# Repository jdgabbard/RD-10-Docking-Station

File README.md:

# RD-10-Docking-Station
A DIY Docking Station for the Casio MX-10 / MX-15 MSX computers

***REV 2 Board Added to Repository***

***See Build Notes file for special instructions!***

Designed to replace or substitute the KB-10 or KB-15 docking station. Future releases may expand this design. For now, consider it a way to have more than one catridge in your MX-10 or MX-15 at a time.  ***For details, see below.***

Features include:<br><br>
-The ability to directly power the Mx-10 / MX-15 / MX-101 computer from the RD-10 Docking Station.<br>
-Integrated Power Switch for turning on the MX-10.<br>
-Experimental Audio Input Jack (2.5mm) for injecting music into the MSX audio amplifier.<br>
-External Power Connector, allowing powering of Floppy Drives directly from the Docking Station.<br>
-Two Primary Slots<br>
-Construction consisting of off the shelf TTL logic, and current production PLD (ATF22V10).<br>
-Implements +12v/-12v rails, so Audio Cartridges work correctly (MX-10 did not do this on it's one cartridge slot).<br><br>

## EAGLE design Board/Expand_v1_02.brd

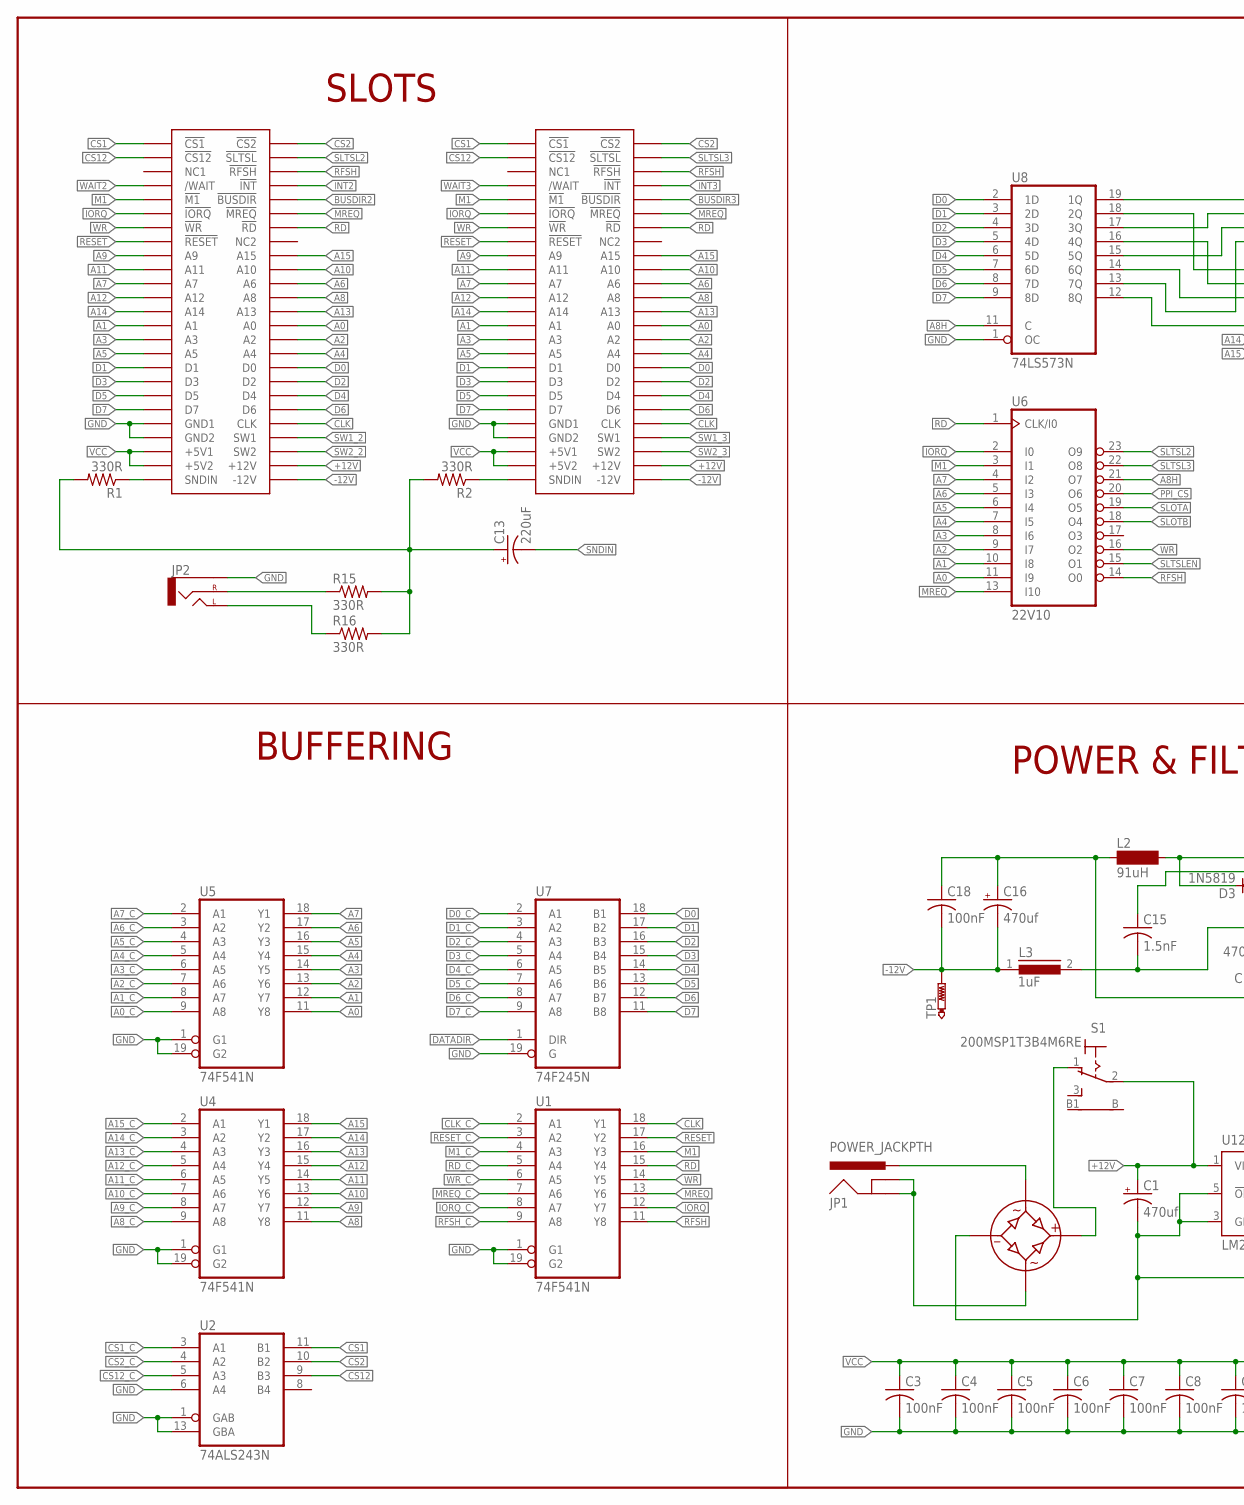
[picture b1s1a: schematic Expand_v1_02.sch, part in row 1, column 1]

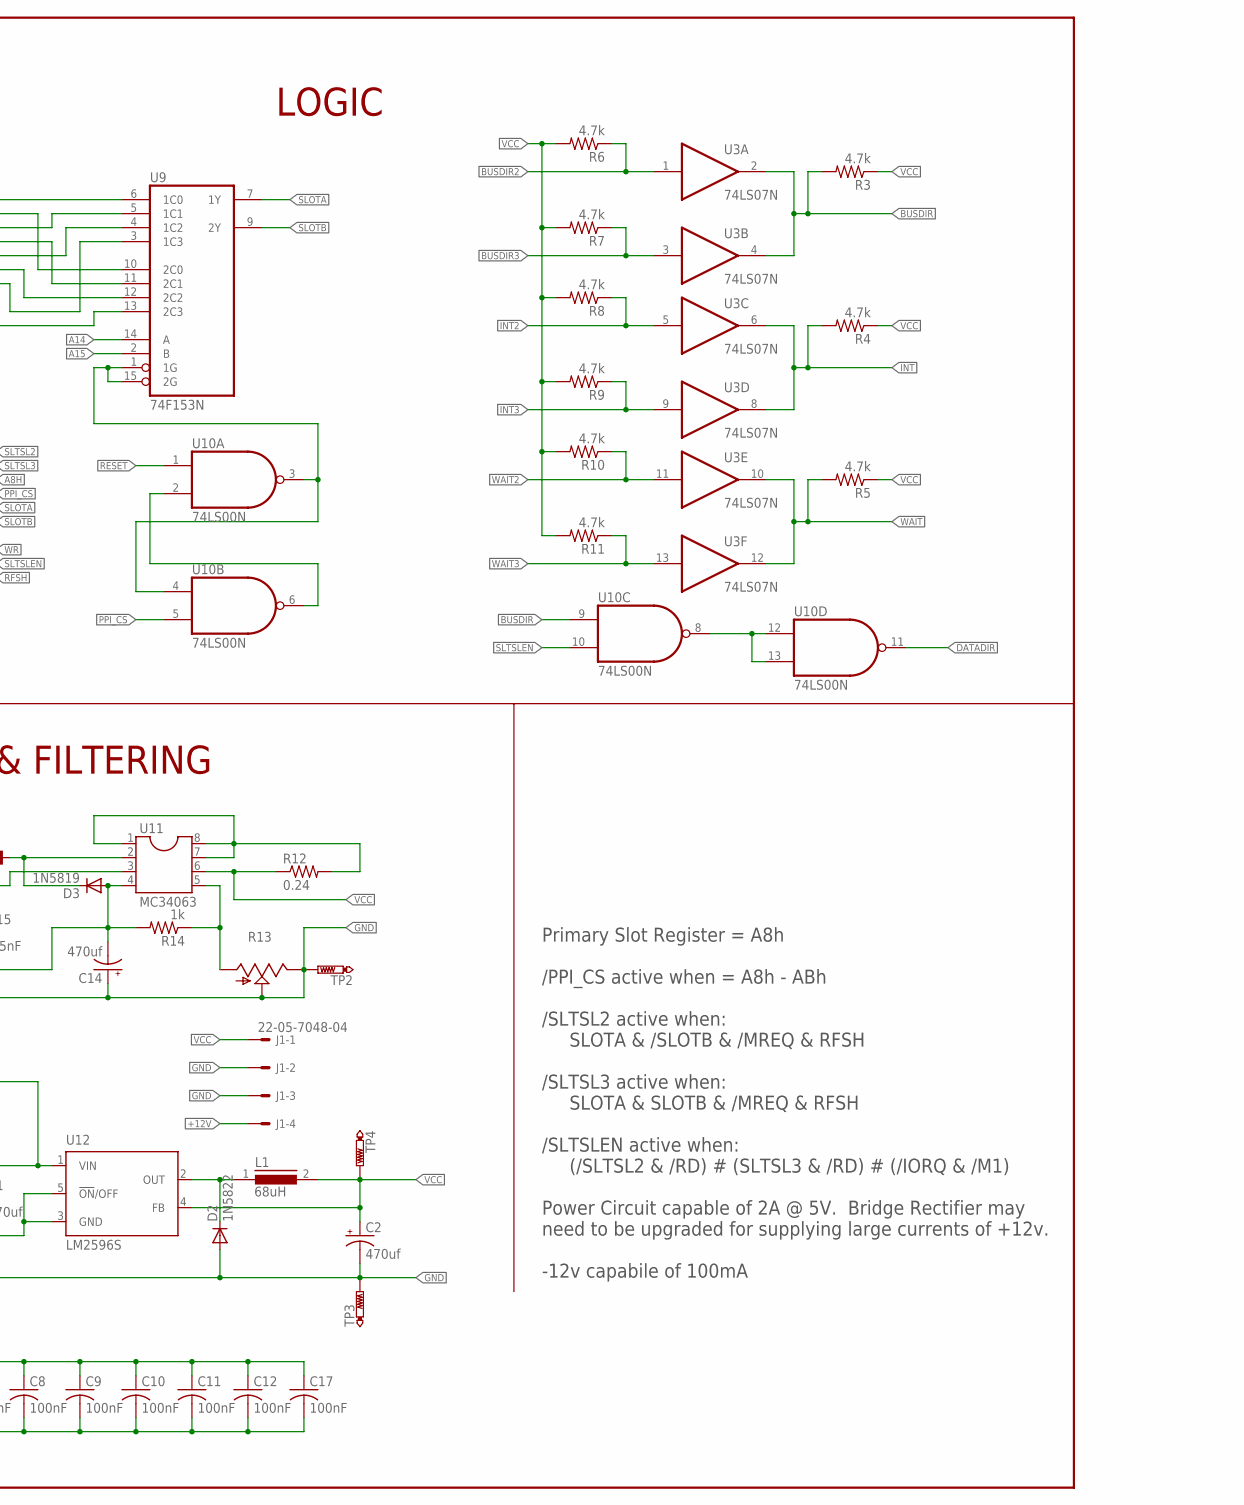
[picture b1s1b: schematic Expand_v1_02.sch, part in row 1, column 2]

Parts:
C1, C2, C14, C16: 470uf; E5-10,5
C3, C4, C5, C6, C7, C8, C9, C10, C11, C12, C17, C18: 100nF; C050-030X075
C13: 220uF; E2-4
C15: 1.5nF; C050-030X075
CONN2, CONN3: MSX_CART_SLOT; CART_SLOT
D1: 2W10
D2: 1N5822; DO201-15
D3: 1N5819; DO15-12
J1: 22-05-7048-04; 7395-04
JP1: POWER_JACKPTH; POWER_JACK_PTH
JP2: AUDIO-JACK1:1; STEREOJACK2.5MM
L1: 68uH; A26GFC
L2: 91uH; BS11
L3: 1uF; MCC10
R1, R2, R15, R16: 330R; 0207/7
R3, R4, R5, R6, R7, R8, R9, R10, R11: 4.7k; 0207/7
R12: 0.24; 0207/10
R13: TRIM_US-RJ9W; RJ9W
R14: 1k; 0207/7
S1: 200MSP1T3B4M6RE; 9070-1W
TP1, TP2, TP3, TP4: PTR1B2,54; B2,54
U1, U4, U5: 74F541N; DIL20
U2: 74ALS243N; DIL14
U3: 74LS07N; DIL14
U6: 22V10; DIL24-3
U7: 74F245N; DIL20
U8: 74LS573N; DIL20
U9: 74F153N; DIL16
U10: 74LS00N; DIL14
U11: MC34063; DIL08
U12: LM2596S; TO263-5

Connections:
!A8H: U6.21 (O7), U8.11 (C)
!BUSDIR: R3.2, U3.2 (O), U3.4 (O), U10.9 (I0)
!BUSDIR2: CONN2.P$10 (!BUSDIR), R6.1, U3.1 (I)
!BUSDIR3: CONN3.P$10 (!BUSDIR), R7.1, U3.3 (I)
!CS1: CONN2.P$1 (!CS1), CONN3.P$1 (!CS1), U2.11 (B1)
!CS1_C: U2.3 (A1)
!CS2: CONN2.P$2 (!CS2), CONN3.P$2 (!CS2), U2.10 (B2)
!CS2_C: U2.4 (A2)
!CS12: CONN2.P$3 (!CS12), CONN3.P$3 (!CS12), U2.9 (B3)
!CS12_C: U2.5 (A3)
!DATADIR: U7.1 (DIR), U10.11 (O)
!INT: R4.2, U3.6 (O), U3.8 (O)
!INT2: CONN2.P$8 (!INT), R8.1, U3.5 (I)
!INT3: CONN3.P$8 (!INT), R9.1, U3.9 (I)
!IORQ: CONN2.P$11 (!IORQ), CONN3.P$11 (!IORQ), U1.12 (Y7), U6.2 (I0)
!IORQ_C: U1.8 (A7)
!M1: CONN2.P$9 (!M1), CONN3.P$9 (!M1), U1.16 (Y3), U6.3 (I1)
!M1_C: U1.4 (A3)
!MREQ: CONN2.P$12 (!MREQ), CONN3.P$12 (!MREQ), U1.13 (Y6), U6.13 (I10)
!MREQ_C: U1.7 (A6)
!PPI_CS: U6.20 (O6), U10.5 (I1)
!RD: CONN2.P$14 (!RD), CONN3.P$14 (!RD), U1.15 (Y4), U6.1 (CLK/I0)
!RD_C: U1.5 (A4)
!RESET: CONN2.P$15 (!RESET), CONN3.P$15 (!RESET), U1.17 (Y2), U10.1 (I0)
!RESET_C: U1.3 (A2)
!RFSH: CONN2.P$6 (!RFSH), CONN3.P$6 (!RFSH), U1.11 (Y8), U6.14 (O0)
!RFSH_C: U1.9 (A8)
!SLTSL2: CONN2.P$4 (!SLTSL), U6.23 (O9)
!SLTSL3: CONN3.P$4 (!SLTSL), U6.22 (O8)
!SLTSLEN: U6.15 (O1), U10.10 (I1)
!WAIT: R5.2, U3.10 (O), U3.12 (O)
!WAIT2: CONN2.P$7 (/WAIT), R10.1, U3.11 (I)
!WAIT3: CONN3.P$7 (/WAIT), R11.1, U3.13 (I)
!WR: CONN2.P$13 (!WR), CONN3.P$13 (!WR), U1.14 (Y5), U6.16 (O2)
!WR_C: U1.6 (A5)
+12V: C1.+, CONN2.P$48 (+12V), CONN3.P$48 (+12V), J1.4, S1.2, U12.1 (VIN)
-12V: C16.-, C18.2, CONN2.P$50 (-12V), CONN3.P$50 (-12V), L3.1, TP1.TP
A0: CONN2.P$28 (A0), CONN3.P$28 (A0), U5.11 (Y8), U6.11 (I9)
A0_C: U5.9 (A8)
A1: CONN2.P$27 (A1), CONN3.P$27 (A1), U5.12 (Y7), U6.10 (I8)
A1_C: U5.8 (A7)
A2: CONN2.P$30 (A2), CONN3.P$30 (A2), U5.13 (Y6), U6.9 (I7)
A2_C: U5.7 (A6)
A3: CONN2.P$29 (A3), CONN3.P$29 (A3), U5.14 (Y5), U6.8 (I6)
A3_C: U5.6 (A5)
A4: CONN2.P$32 (A4), CONN3.P$32 (A4), U5.15 (Y4), U6.7 (I5)
A4_C: U5.5 (A4)
A5: CONN2.P$31 (A5), CONN3.P$31 (A5), U5.16 (Y3), U6.6 (I4)
A5_C: U5.4 (A3)
A6: CONN2.P$22 (A6), CONN3.P$22 (A6), U5.17 (Y2), U6.5 (I3)
A6_C: U5.3 (A2)
A7: CONN2.P$21 (A7), CONN3.P$21 (A7), U5.18 (Y1), U6.4 (I2)
A7_C: U5.2 (A1)
A8: CONN2.P$24 (A8), CONN3.P$24 (A8), U4.11 (Y8)
A8_C: U4.9 (A8)
A9: CONN2.P$17 (A9), CONN3.P$17 (A9), U4.12 (Y7)
A9_C: U4.8 (A7)
A10: CONN2.P$20 (A10), CONN3.P$20 (A10), U4.13 (Y6)
A10_C: U4.7 (A6)
A11: CONN2.P$19 (A11), CONN3.P$19 (A11), U4.14 (Y5)
A11_C: U4.6 (A5)
A12: CONN2.P$23 (A12), CONN3.P$23 (A12), U4.15 (Y4)
A12_C: U4.5 (A4)
A13: CONN2.P$26 (A13), CONN3.P$26 (A13), U4.16 (Y3)
A13_C: U4.4 (A3)
A14: CONN2.P$25 (A14), CONN3.P$25 (A14), U4.17 (Y2), U9.14 (A)
A14_C: U4.3 (A2)
A15: CONN2.P$18 (A15), CONN3.P$18 (A15), U4.18 (Y1), U9.2 (B)
A15_C: U4.2 (A1)
CLK: CONN2.P$42 (CLK), CONN3.P$42 (CLK), U1.18 (Y1)
CLK_C: U1.2 (A1)
D0: CONN2.P$34 (D0), CONN3.P$34 (D0), U7.18 (B1), U8.2 (1D)
D0_C: U7.2 (A1)
D1: CONN2.P$33 (D1), CONN3.P$33 (D1), U7.17 (B2), U8.3 (2D)
D1_C: U7.3 (A2)
D2: CONN2.P$36 (D2), CONN3.P$36 (D2), U7.16 (B3), U8.4 (3D)
D2_C: U7.4 (A3)
D3: CONN2.P$35 (D3), CONN3.P$35 (D3), U7.15 (B4), U8.5 (4D)
D3_C: U7.5 (A4)
D4: CONN2.P$38 (D4), CONN3.P$38 (D4), U7.14 (B5), U8.6 (5D)
D4_C: U7.6 (A5)
D5: CONN2.P$37 (D5), CONN3.P$37 (D5), U7.13 (B6), U8.7 (6D)
D5_C: U7.7 (A6)
D6: CONN2.P$40 (D6), CONN3.P$40 (D6), U7.12 (B7), U8.8 (7D)
D6_C: U7.8 (A7)
D7: CONN2.P$39 (D7), CONN3.P$39 (D7), U7.11 (B8), U8.9 (8D)
D7_C: U7.9 (A8)
GND: C1.-, C2.-, C3.2, C4.2, C5.2, C6.2, C7.2, C8.2, C9.2, C10.2, C11.2, C12.2, C14.+, C16.+, C17.2, C18.1, CONN2.P$41 (GND1), CONN2.P$43 (GND2), CONN3.P$41 (GND1), CONN3.P$43 (GND2), D1.P$4, D2.A, J1.2, J1.3, JP2.5 (SLEEVE), L2.1, R13.E, R13.S, TP2.TP, TP3.TP, U1.1 (G1), U1.10 (GND), U1.19 (G2), U2.1 (GAB), U2.6 (A4), U2.7 (GND), U2.13 (GBA), U3.7 (GND), U4.1 (G1), U4.10 (GND), U4.19 (G2), U5.1 (G1), U5.10 (GND), U5.19 (G2), U6.12 (GND), U7.10 (GND), U7.19 (G), U8.1 (OC), U8.10 (GND), U9.8 (GND), U10.7 (GND), U12.3 (GND), U12.5 (!ON!/OFF)
unnamed: CONN3.P$49 (SNDIN), R2.1
unnamed: CONN2.P$49 (SNDIN), R1.1
unnamed: U8.19 (1Q), U9.6 (1C0)
unnamed: C13.+, R1.2, R2.2, R15.2, R16.2
unnamed: U8.18 (2Q), U9.10 (2C0)
unnamed: U8.17 (3Q), U9.5 (1C1)
unnamed: U8.16 (4Q), U9.11 (2C1)
unnamed: U8.15 (5Q), U9.4 (1C2)
unnamed: U8.14 (6Q), U9.12 (2C2)
unnamed: U8.13 (7Q), U9.3 (1C3)
unnamed: U8.12 (8Q), U9.13 (2C3)
unnamed: U10.2 (I1), U10.6 (O)
unnamed: U9.1 (1G), U9.15 (2G), U10.3 (O), U10.4 (I0)
unnamed: U10.8 (O), U10.12 (I0), U10.13 (I1)
unnamed: D1.P$2, S1.1 (O)
unnamed: R12.2, U11.1, U11.7, U11.8
unnamed: JP2.4 (RIGHT), R15.1
unnamed: R13.A, R14.1, U11.5
unnamed: D1.P$1, JP1.PWR
unnamed: D1.P$3, JP1.GND, JP1.GNDBREAK
unnamed: C14.-, C15.2, D3.A, L3.2, R14.2, U11.4
unnamed: C15.1, U11.3
unnamed: D3.C, L2.2, U11.2
unnamed: JP2.1 (LEFT), R16.1
unnamed: D2.C, L1.1, U12.2 (OUT)
SLOTA: U6.19 (O5), U9.7 (1Y)
SLOTB: U6.18 (O4), U9.9 (2Y)
SNDIN: C13.-
SW1_2: CONN2.P$44 (SW1)
SW1_3: CONN3.P$44 (SW1)
SW2_2: CONN2.P$46 (SW2)
SW2_3: CONN3.P$46 (SW2)
VCC: C2.+, C3.1, C4.1, C5.1, C6.1, C7.1, C8.1, C9.1, C10.1, C11.1, C12.1, C17.1, CONN2.P$45 (+5V1), CONN2.P$47 (+5V2), CONN3.P$45 (+5V1), CONN3.P$47 (+5V2), J1.1, L1.2, R3.1, R4.1, R5.1, R6.2, R7.2, R8.2, R9.2, R10.2, R11.2, R12.1, TP4.TP, U1.20 (VCC), U2.14 (VCC), U3.14 (VCC), U4.20 (VCC), U5.20 (VCC), U6.24 (VCC), U7.20 (VCC), U8.20 (VCC), U9.16 (VCC), U10.14 (VCC), U11.6, U12.4 (FB)

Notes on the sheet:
SLOTS
LOGIC
BUFFERING
POWER & FILTERING
Primary Slot Register = A8h /PPI_CS active when = A8h - ABh /SLTSL2 active when: SLOTA & /SLOTB & /MREQ & RFSH /SLTSL3 active when: SLOTA & SLOTB & /MREQ & RFSH /SLTSLEN active when: (/SLTSL2 & /RD) # (SLTSL3 & /RD) # (/IORQ & /M1) Power Circuit capable of 2A @ 5V. Bridge Rectifier may need to be u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

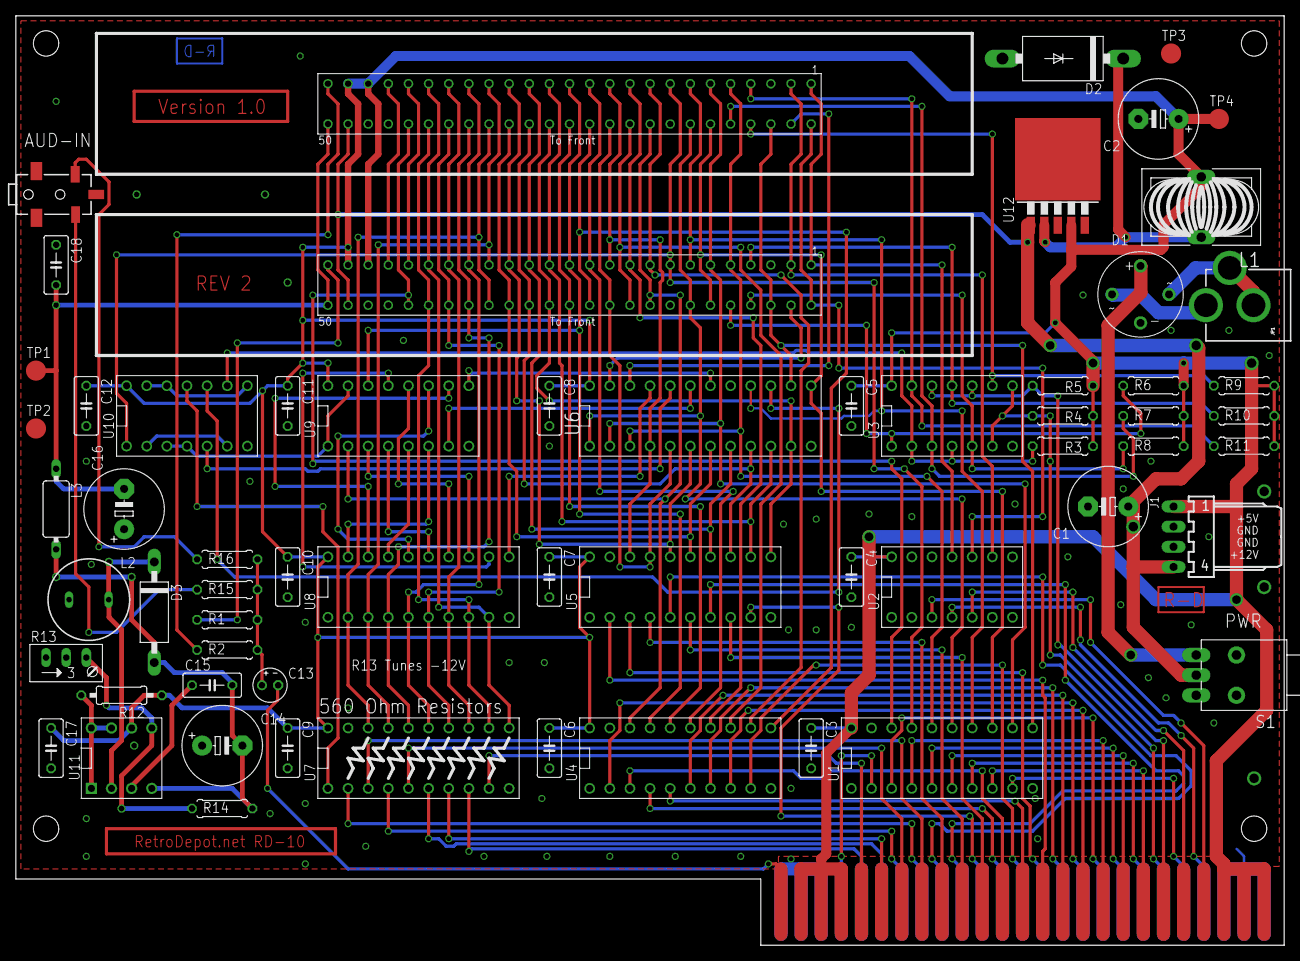
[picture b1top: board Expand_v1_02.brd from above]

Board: 2 copper layers, 160.0 x 117.2 mm, 62 parts (0 on the bottom side), 81 nets.

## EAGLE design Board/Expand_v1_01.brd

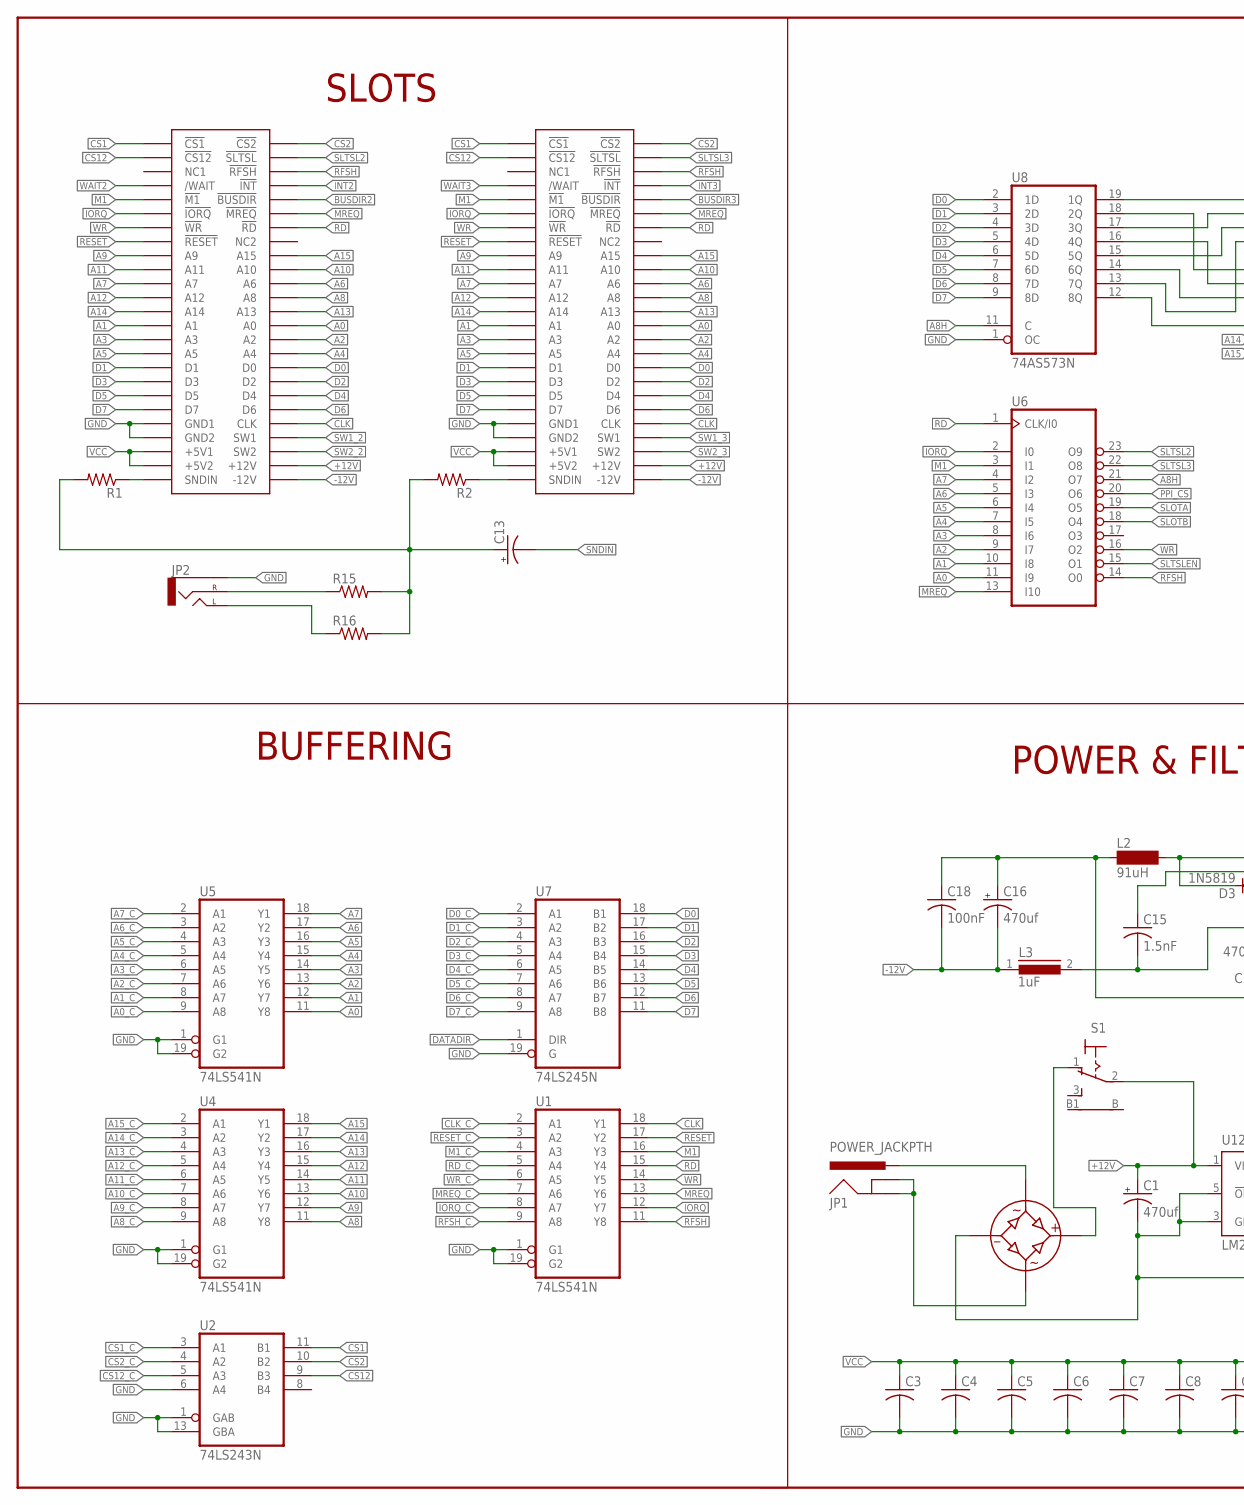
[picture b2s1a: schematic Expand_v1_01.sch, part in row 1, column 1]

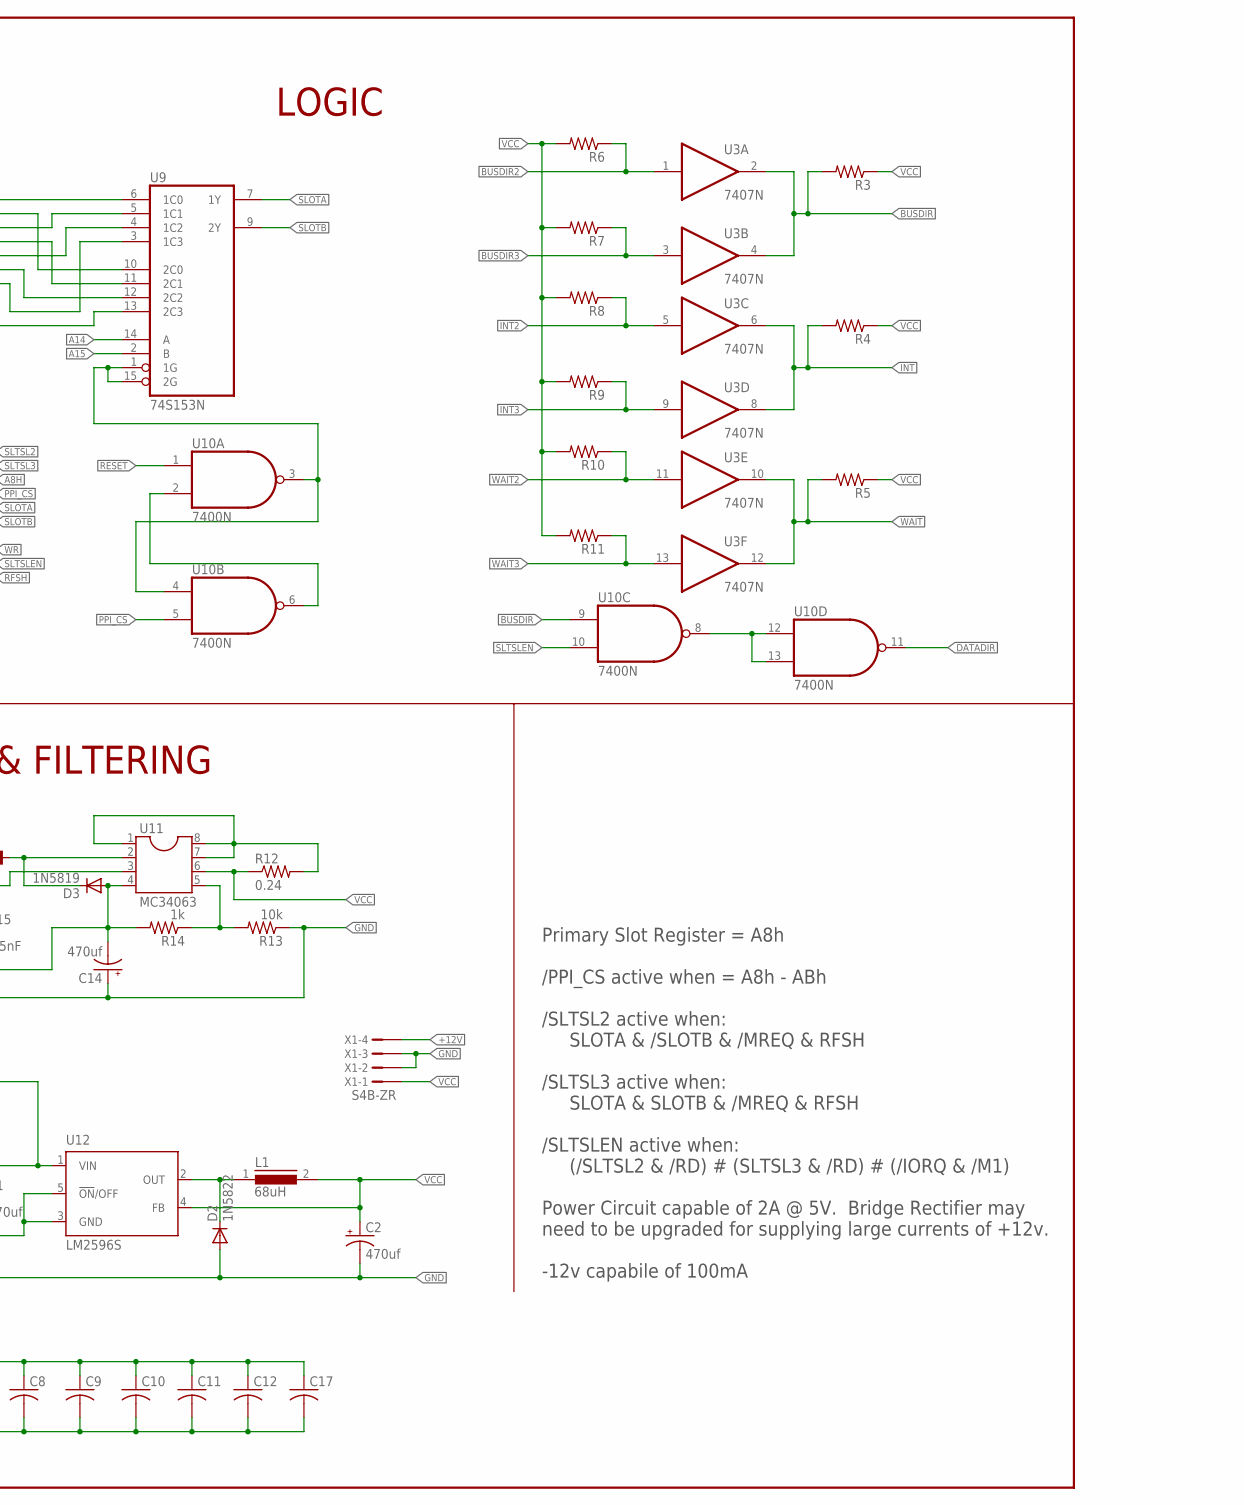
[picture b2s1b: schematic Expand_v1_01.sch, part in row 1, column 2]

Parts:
C1, C2, C14, C16: 470uf; E5-10,5
C3, C4, C5, C6, C7, C8, C9, C10, C11, C12, C17: C-US050-030X075; C050-030X075
C13: CPOL-USE2-4; E2-4
C15: 1.5nF; C050-030X075
C18: 100nF; C050-030X075
D1: 2W10
D2: 1N5822; DO201-15
D3: 1N5819; DO15-12
JP1: POWER_JACKPTH; POWER_JACK_PTH
JP2: AUDIO-JACK1:1; STEREOJACK2.5MM
L1: 68uH; A26GFC
L2: 91uH; BS11
L3: 1uF; MCC10
R1, R2, R3, R4, R5, R6, R7, R8, R9, R10, R11, R15, R16: R-US_0207/7; 0207/7
R12: 0.24; 0207/7
R13: 10k; 0207/7
R14: 1k; 0207/7
S1: 9070-1W
U1, U4, U5: 74LS541N; DIL20
U2: 74LS243N; DIL14
U3: 7407N; DIL14
U6: 22V10; DIL24-3
U7: 74LS245N; DIL20
U8: 74AS573N; DIL20
U9: 74S153N; DIL16
U10: 7400N; DIL14
U11: MC34063; DIL08
U12: LM2596S; TO263-5
U$1, U$2: MSX_CART_SLOT; CART_SLOT
X1: S4B-ZR

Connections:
!A8H: U6.21 (O7), U8.11 (C)
!BUSDIR: R3.2, U3.2 (O), U3.4 (O), U10.9 (I0)
!BUSDIR2: R6.1, U3.1 (I), U$1.P$10 (!BUSDIR)
!BUSDIR3: R7.1, U3.3 (I), U$2.P$10 (!BUSDIR)
!CS1: U2.11 (B1), U$1.P$1 (!CS1), U$2.P$1 (!CS1)
!CS1_C: U2.3 (A1)
!CS2: U2.10 (B2), U$1.P$2 (!CS2), U$2.P$2 (!CS2)
!CS2_C: U2.4 (A2)
!CS12: U2.9 (B3), U$1.P$3 (!CS12), U$2.P$3 (!CS12)
!CS12_C: U2.5 (A3)
!DATADIR: U7.1 (DIR), U10.11 (O)
!INT: R4.2, U3.6 (O), U3.8 (O)
!INT2: R8.1, U3.5 (I), U$1.P$8 (!INT)
!INT3: R9.1, U3.9 (I), U$2.P$8 (!INT)
!IORQ: U1.12 (Y7), U6.2 (I0), U$1.P$11 (!IORQ), U$2.P$11 (!IORQ)
!IORQ_C: U1.8 (A7)
!M1: U1.16 (Y3), U6.3 (I1), U$1.P$9 (!M1), U$2.P$9 (!M1)
!M1_C: U1.4 (A3)
!MREQ: U1.13 (Y6), U6.13 (I10), U$1.P$12 (!MREQ), U$2.P$12 (!MREQ)
!MREQ_C: U1.7 (A6)
!PPI_CS: U6.20 (O6), U10.5 (I1)
!RD: U1.15 (Y4), U6.1 (CLK/I0), U$1.P$14 (!RD), U$2.P$14 (!RD)
!RD_C: U1.5 (A4)
!RESET: U1.17 (Y2), U10.1 (I0), U$1.P$15 (!RESET), U$2.P$15 (!RESET)
!RESET_C: U1.3 (A2)
!RFSH: U1.11 (Y8), U6.14 (O0), U$1.P$6 (!RFSH), U$2.P$6 (!RFSH)
!RFSH_C: U1.9 (A8)
!SLTSL2: U6.23 (O9), U$1.P$4 (!SLTSL)
!SLTSL3: U6.22 (O8), U$2.P$4 (!SLTSL)
!SLTSLEN: U6.15 (O1), U10.10 (I1)
!WAIT: R5.2, U3.10 (O), U3.12 (O)
!WAIT2: R10.1, U3.11 (I), U$1.P$7 (/WAIT)
!WAIT3: R11.1, U3.13 (I), U$2.P$7 (/WAIT)
!WR: U1.14 (Y5), U6.16 (O2), U$1.P$13 (!WR), U$2.P$13 (!WR)
!WR_C: U1.6 (A5)
+12V: C1.+, S1.2, U12.1 (VIN), U$1.P$48 (+12V), U$2.P$48 (+12V), X1.4
-12V: C16.-, C18.2, L3.1, U$1.P$50 (-12V), U$2.P$50 (-12V)
A0: U5.11 (Y8), U6.11 (I9), U$1.P$28 (A0), U$2.P$28 (A0)
A0_C: U5.9 (A8)
A1: U5.12 (Y7), U6.10 (I8), U$1.P$27 (A1), U$2.P$27 (A1)
A1_C: U5.8 (A7)
A2: U5.13 (Y6), U6.9 (I7), U$1.P$30 (A2), U$2.P$30 (A2)
A2_C: U5.7 (A6)
A3: U5.14 (Y5), U6.8 (I6), U$1.P$29 (A3), U$2.P$29 (A3)
A3_C: U5.6 (A5)
A4: U5.15 (Y4), U6.7 (I5), U$1.P$32 (A4), U$2.P$32 (A4)
A4_C: U5.5 (A4)
A5: U5.16 (Y3), U6.6 (I4), U$1.P$31 (A5), U$2.P$31 (A5)
A5_C: U5.4 (A3)
A6: U5.17 (Y2), U6.5 (I3), U$1.P$22 (A6), U$2.P$22 (A6)
A6_C: U5.3 (A2)
A7: U5.18 (Y1), U6.4 (I2), U$1.P$21 (A7), U$2.P$21 (A7)
A7_C: U5.2 (A1)
A8: U4.11 (Y8), U$1.P$24 (A8), U$2.P$24 (A8)
A8_C: U4.9 (A8)
A9: U4.12 (Y7), U$1.P$17 (A9), U$2.P$17 (A9)
A9_C: U4.8 (A7)
A10: U4.13 (Y6), U$1.P$20 (A10), U$2.P$20 (A10)
A10_C: U4.7 (A6)
A11: U4.14 (Y5), U$1.P$19 (A11), U$2.P$19 (A11)
A11_C: U4.6 (A5)
A12: U4.15 (Y4), U$1.P$23 (A12), U$2.P$23 (A12)
A12_C: U4.5 (A4)
A13: U4.16 (Y3), U$1.P$26 (A13), U$2.P$26 (A13)
A13_C: U4.4 (A3)
A14: U4.17 (Y2), U9.14 (A), U$1.P$25 (A14), U$2.P$25 (A14)
A14_C: U4.3 (A2)
A15: U4.18 (Y1), U9.2 (B), U$1.P$18 (A15), U$2.P$18 (A15)
A15_C: U4.2 (A1)
CLK: U1.18 (Y1), U$1.P$42 (CLK), U$2.P$42 (CLK)
CLK_C: U1.2 (A1)
D0: U7.18 (B1), U8.2 (1D), U$1.P$34 (D0), U$2.P$34 (D0)
D0_C: U7.2 (A1)
D1: U7.17 (B2), U8.3 (2D), U$1.P$33 (D1), U$2.P$33 (D1)
D1_C: U7.3 (A2)
D2: U7.16 (B3), U8.4 (3D), U$1.P$36 (D2), U$2.P$36 (D2)
D2_C: U7.4 (A3)
D3: U7.15 (B4), U8.5 (4D), U$1.P$35 (D3), U$2.P$35 (D3)
D3_C: U7.5 (A4)
D4: U7.14 (B5), U8.6 (5D), U$1.P$38 (D4), U$2.P$38 (D4)
D4_C: U7.6 (A5)
D5: U7.13 (B6), U8.7 (6D), U$1.P$37 (D5), U$2.P$37 (D5)
D5_C: U7.7 (A6)
D6: U7.12 (B7), U8.8 (7D), U$1.P$40 (D6), U$2.P$40 (D6)
D6_C: U7.8 (A7)
D7: U7.11 (B8), U8.9 (8D), U$1.P$39 (D7), U$2.P$39 (D7)
D7_C: U7.9 (A8)
GND: C1.-, C2.-, C3.2, C4.2, C5.2, C6.2, C7.2, C8.2, C9.2, C10.2, C11.2, C12.2, C14.+, C16.+, C17.2, C18.1, D1.P$4, D2.A, JP2.5 (SLEEVE), L2.1, R13.1, U1.1 (G1), U1.10 (GND), U1.19 (G2), U2.1 (GAB), U2.6 (A4), U2.7 (GND), U2.13 (GBA), U3.7 (GND), U4.1 (G1), U4.10 (GND), U4.19 (G2), U5.1 (G1), U5.10 (GND), U5.19 (G2), U6.12 (GND), U7.10 (GND), U7.19 (G), U8.1 (OC), U8.10 (GND), U9.8 (GND), U10.7 (GND), U12.3 (GND), U12.5 (!ON!/OFF), U$1.P$41 (GND1), U$1.P$43 (GND2), U$2.P$41 (GND1), U$2.P$43 (GND2), X1.2, X1.3
unnamed: R2.1, U$2.P$49 (SNDIN)
unnamed: R1.1, U$1.P$49 (SNDIN)
unnamed: U8.19 (1Q), U9.6 (1C0)
unnamed: C13.+, R1.2, R2.2, R15.2, R16.2
unnamed: U8.18 (2Q), U9.10 (2C0)
unnamed: U8.17 (3Q), U9.5 (1C1)
unnamed: U8.16 (4Q), U9.11 (2C1)
unnamed: U8.15 (5Q), U9.4 (1C2)
unnamed: U8.14 (6Q), U9.12 (2C2)
unnamed: U8.13 (7Q), U9.3 (1C3)
unnamed: U8.12 (8Q), U9.13 (2C3)
unnamed: U10.2 (I1), U10.6 (O)
unnamed: U9.1 (1G), U9.15 (2G), U10.3 (O), U10.4 (I0)
unnamed: U10.8 (O), U10.12 (I0), U10.13 (I1)
unnamed: D1.P$2, S1.1 (O)
unnamed: R12.2, U11.1, U11.7, U11.8
unnamed: JP2.4 (RIGHT), R15.1
unnamed: R13.2, R14.1, U11.5
unnamed: D1.P$1, JP1.PWR
unnamed: D1.P$3, JP1.GND, JP1.GNDBREAK
unnamed: C14.-, C15.2, D3.A, L3.2, R14.2, U11.4
unnamed: C15.1, U11.3
unnamed: D3.C, L2.2, U11.2
unnamed: JP2.1 (LEFT), R16.1
unnamed: D2.C, L1.1, U12.2 (OUT)
SLOTA: U6.19 (O5), U9.7 (1Y)
SLOTB: U6.18 (O4), U9.9 (2Y)
SNDIN: C13.-
SW1_2: U$1.P$44 (SW1)
SW1_3: U$2.P$44 (SW1)
SW2_2: U$1.P$46 (SW2)
SW2_3: U$2.P$46 (SW2)
VCC: C2.+, C3.1, C4.1, C5.1, C6.1, C7.1, C8.1, C9.1, C10.1, C11.1, C12.1, C17.1, L1.2, R3.1, R4.1, R5.1, R6.2, R7.2, R8.2, R9.2, R10.2, R11.2, R12.1, U1.20 (VCC), U2.14 (VCC), U3.14 (VCC), U4.20 (VCC), U5.20 (VCC), U6.24 (VCC), U7.20 (VCC), U8.20 (VCC), U9.16 (VCC), U10.14 (VCC), U11.6, U12.4 (FB), U$1.P$45 (+5V1), U$1.P$47 (+5V2), U$2.P$45 (+5V1), U$2.P$47 (+5V2), X1.1

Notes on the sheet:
SLOTS
LOGIC
BUFFERING
POWER & FILTERING
Primary Slot Register = A8h /PPI_CS active when = A8h - ABh /SLTSL2 active when: SLOTA & /SLOTB & /MREQ & RFSH /SLTSL3 active when: SLOTA & SLOTB & /MREQ & RFSH /SLTSLEN active when: (/SLTSL2 & /RD) # (SLTSL3 & /RD) # (/IORQ & /M1) Power Circuit capable of 2A @ 5V. Bridge Rectifier may need to be u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

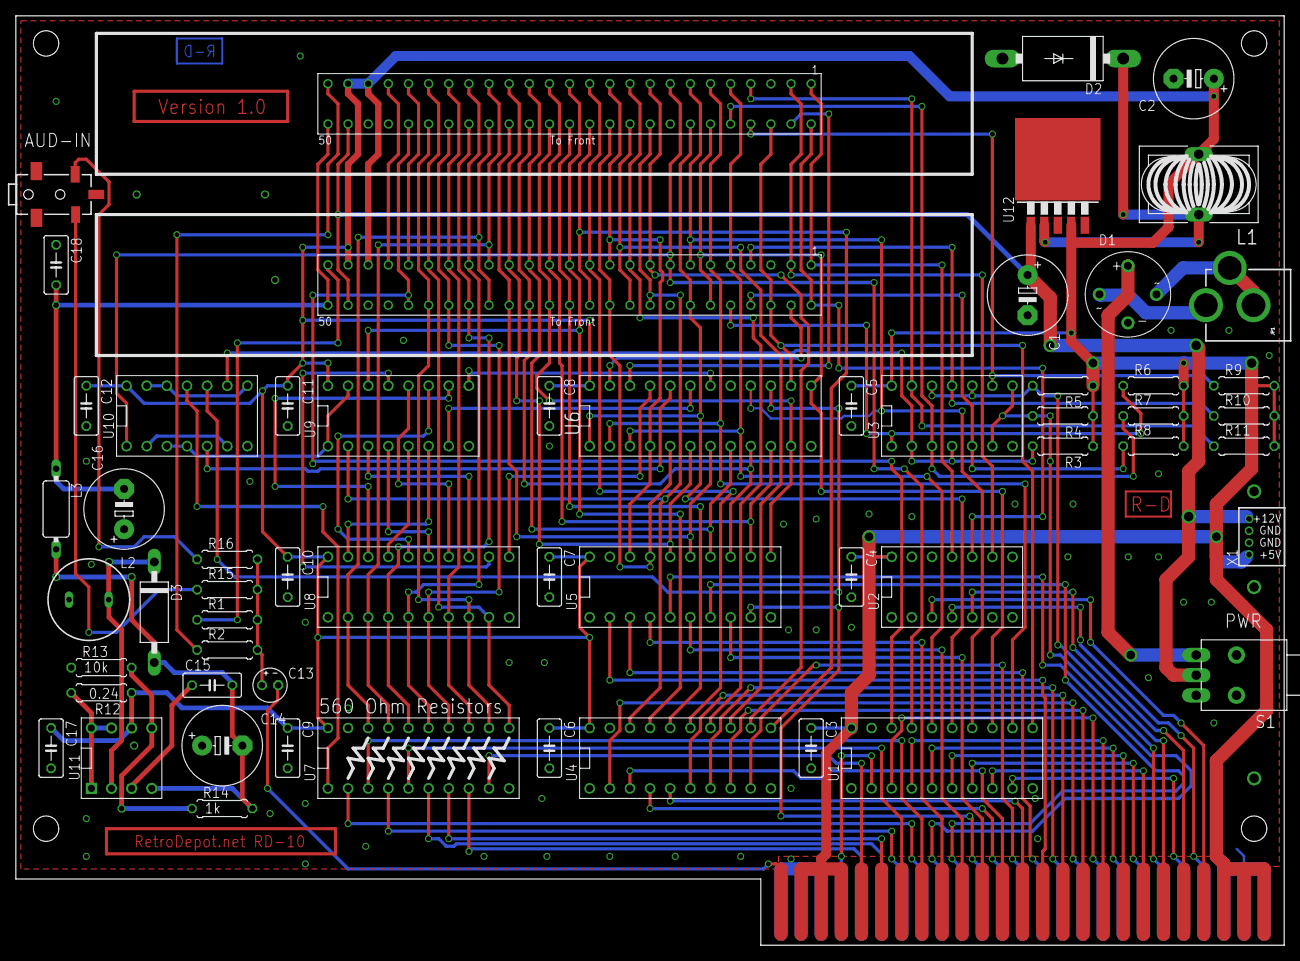
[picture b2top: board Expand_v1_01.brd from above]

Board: 2 copper layers, 160.0 x 117.2 mm, 58 parts (0 on the bottom side), 81 nets.

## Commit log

2022-01-16 Initial Upload
    Upload of initial files.
2022-02-23 Feb 22 Update
    Preliminary BOM, Added 3d Printable Case
2022-07-26 Add files via upload
    Added photos of completed docking station with enclosure.
2022-07-26 Update README.md
    Included Pictures of the completed docking station, as well as feature list.
2022-07-27 Add files via upload
    U7 instructions picture.
2022-07-27 Update Build Notes.md
    Added information about U7
2022-07-27 Update README.md
    Added instruction to see build notes file.
2022-07-27 Update BOM.xls
    Updated BOM to reflect U7 instructions.
2022-08-10 Update BOM.xls
    Updated C15 Part number from 15nF capacitor to 1.5nF capacitor.
2022-09-08 New Versions of 3d Printable Case
    Resized cases for importation in software which expects sizes in inches.
    Added Readme file describing file versions.
2022-09-09 v1.0 Rev2 PCB Added
    Added new board version, added notes, updated BOM.

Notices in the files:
parts and their libraries:
SparkFun-Connectors: Licensing: Creative Commons ShareAlike 4.0 International - https://creativecommons.org/licenses/by-sa/4.0
